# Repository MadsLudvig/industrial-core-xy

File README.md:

# industrial-core-xy
Large scale 3D printer made with old servomotor parts from CNC cantilever robots

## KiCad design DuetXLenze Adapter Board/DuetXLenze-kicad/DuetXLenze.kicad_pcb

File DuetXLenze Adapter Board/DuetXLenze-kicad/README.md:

# DuetXLenze

### Parts used

__C1 - C4__		JLCPCB Part # C13585

__D1 - D2__		JLCPCB Part # C8598

__FB1 - FB2__	JLCPCB Part # C1015

__J1 - J3__			Farnell Part # 1338747

__R1 - R12__		JLCPCB Part # C28636

__U1__				JLCPCB Part # C6187

__U2__				JLCPCB Part # C6186

__U3 + U5__		JLCPCB Part # C7859

__U4__				JLCPCB Part # C5590

__X1 - X4__		Farnell Part # 2352396

__S1__				Farnel Part # 1123939

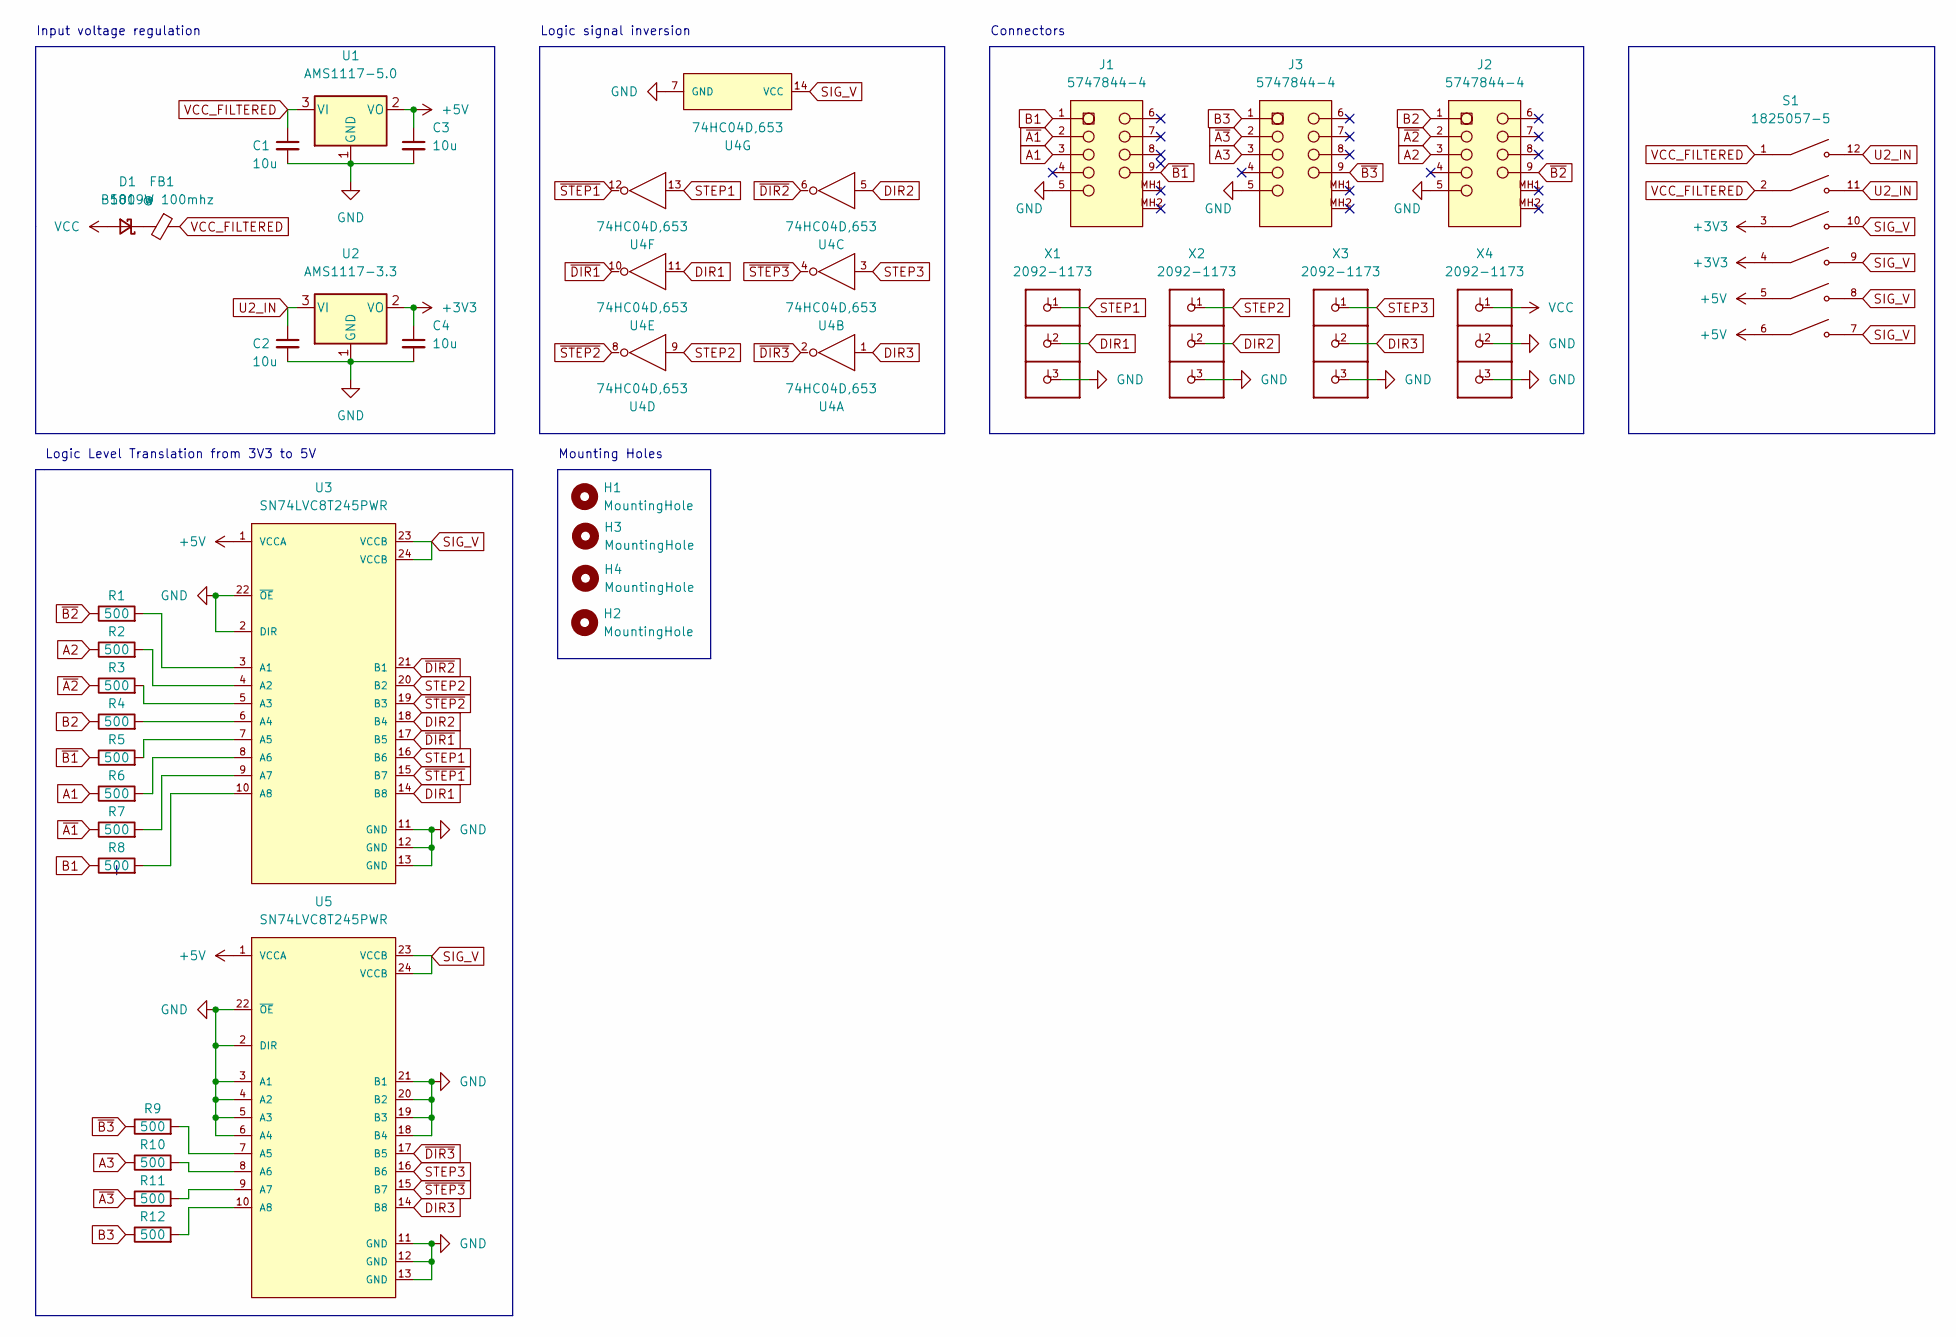
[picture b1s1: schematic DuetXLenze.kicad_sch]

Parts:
C1, C2, C3, C4: 10u; C_1206_3216Metric
D1: B5819W; D_SOD-123
FB1: 100 @ 100mhz; L_0805_2012Metric
H1, H2, H3, H4: MountingHole; MountingHole_4.3mm_M4_Pad_Via
J1, J2, J3: 5747844-4; TE_Connectivity-5747844-4-0
R1, R2, R3, R4, R5, R6, R7, R8, R9, R10, R11, R12: 500; R_0805_2012Metric
S1: 1825057-5; DIP762W56P254L1772H585Q12
U1: AMS1117-5.0; SOT-223-3_TabPin2
U2: AMS1117-3.3; SOT-223-3_TabPin2
U3, U5: SN74LVC8T245PWR; TSSOP-24_4.4x7.8mm_P0.65mm; mouser part number 595-SN74LVC8T245PWR; digikey description IC TRNSLTR BIDIRECTIONAL 24TSSOP
U4: 74HC04D,653; SOIC-14_3.9x8.7mm_P1.27mm; mouser part number 771-74HC04D-T; digikey description IC INVERTER 6CH 6-INP 14SO
X1, X2, X3, X4: 2092-1173; P-2092-1173

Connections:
+3V3: C4.1, S1.3, S1.4, U2.2 (VO)
+5V: C3.1, S1.5, S1.6, U1.2 (VO), U3.1 (VCCA), U5.1 (VCCA)
A1: J1.3, R6.1
A2: J2.3, R2.1
A3: J3.3, R10.1
B1: J1.1, R8.1
B2: J2.1, R4.1
B3: J3.1, R12.1
DIR1: U3.14 (B8), U4.11 (5A), X1.L2
DIR2: U3.18 (B4), U4.5 (3A), X2.L2
DIR3: U4.1 (1A), U5.14 (B8), X3.L2
GND: C1.2, C2.2, C3.2, C4.2, J1.5, J2.5, J3.5, U1.1 (GND), U2.1 (GND), U3.2 (DIR), U3.11 (GND), U3.12 (GND), U3.13 (GND), U3.22 (~OE), U4.7 (GND), U5.2 (DIR), U5.3 (A1), U5.4 (A2), U5.5 (A3), U5.6 (A4), U5.11 (GND), U5.12 (GND), U5.13 (GND), U5.18 (B4), U5.19 (B3), U5.20 (B2), U5.21 (B1), U5.22 (~OE), X1.L3, X2.L3, X3.L3, X4.L2, X4.L3
unnamed: D1.1 (K), FB1.2
unnamed: R1.2, U3.3 (A1)
unnamed: R2.2, U3.4 (A2)
unnamed: R3.2, U3.5 (A3)
unnamed: R4.2, U3.6 (A4)
unnamed: R5.2, U3.7 (A5)
unnamed: R6.2, U3.8 (A6)
unnamed: R7.2, U3.9 (A7)
unnamed: R8.2, U3.10 (A8)
unnamed: R9.2, U5.7 (A5)
unnamed: R10.2, U5.8 (A6)
unnamed: R11.2, U5.9 (A7)
unnamed: R12.2, U5.10 (A8)
SIG_V: S1.7, S1.8, S1.9, S1.10, U3.23 (VCCB), U3.24 (VCCB), U4.14 (VCC), U5.23 (VCCB), U5.24 (VCCB)
STEP1: U3.16 (B6), U4.13 (6A), X1.L1
STEP2: U3.20 (B2), U4.9 (4A), X2.L1
STEP3: U4.3 (2A), U5.16 (B6), X3.L1
U2_IN: C2.1, S1.11, S1.12, U2.3 (VI)
VCC: D1.2 (A), X4.L1
VCC_FILTERED: C1.1, FB1.1, S1.1, S1.2, U1.3 (VI)
~A1: J1.2, R7.1
~A2: J2.2, R3.1
~A3: J3.2, R11.1
~B1: J1.9, R5.1
~B2: J2.9, R1.1
~B3: J3.9, R9.1
~DIR1: U3.17 (B5), U4.10 (5Y)
~DIR2: U3.21 (B1), U4.6 (3Y)
~DIR3: U4.2 (1Y), U5.17 (B5)
~STEP1: U3.15 (B7), U4.12 (6Y)
~STEP2: U3.19 (B3), U4.8 (4Y)
~STEP3: U4.4 (2Y), U5.15 (B7)

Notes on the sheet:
Input voltage regulation
Mounting Holes
Logic Level Translation from 3V3 to 5V
Logic signal inversion
Connectors

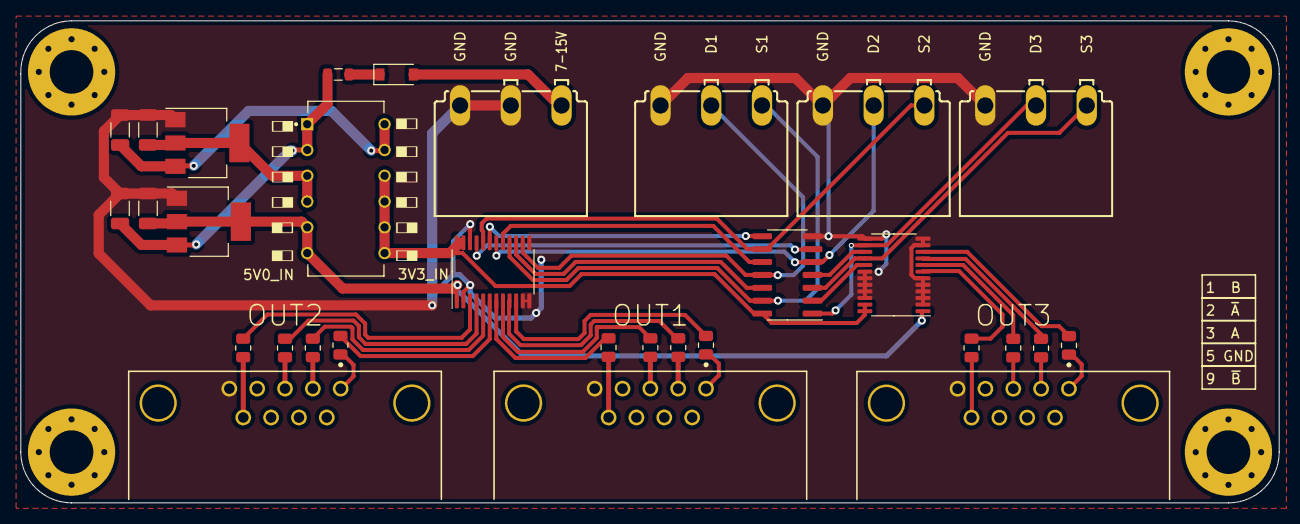
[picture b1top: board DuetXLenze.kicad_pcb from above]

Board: 2 copper layers, 124.0 x 47.5 mm, 35 parts (0 on the bottom side), 44 nets.

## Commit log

2022-08-12 Added files
